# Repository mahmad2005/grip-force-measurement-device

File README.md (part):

# Hand Grip Force and Trajectory Measurement System

## Overview

This project focuses on the development of a portable, intelligent device designed to measure **hand grip force** and **object trajectory** for neurological assessment, particularly in patients with **stroke** or **Multiple Sclerosis (MS)**.

## Key Features

- 🧠 **Neurological Focus**  
  Designed to evaluate motor function, coordination, and rehabilitation progress in stroke and MS patients.

- 🔧 **Core Technologies**
  - **STM32 Microcontrollers** – Real-time data acquisition and processing
  - **Pressure Sensors** – High-resolution spatial grip force measurement
  - **Gyroscope & IMU Sensors** – Motion and orientation tracking of held objects
  - **Bluetooth** – Wireless data transmission to PC/mobile apps
  - **RTOS** – Deterministic multitasking on embedded systems
  - **Embedded Linux** – Advanced data handling and UI support

## System Architecture

[ Pressure Sensor ] [ Gyroscope / IMU ]
| |
[ Analog Front End ] |
| |
[ STM32 MCU ] <--> [ Bluetooth Module ]
|
[ Data Logger / Wi-Fi ]
|
[ Embedded Linux Platform ]

## Use Case

The system enables clinicians and researchers to:
- Quantitatively assess hand grip strength and control
- Track and visualize object movement during gripping tasks
- Analyze neuromuscular impairments and rehabilitation outcomes

## Future Work

- 🔬 Integration with AI models for predictive analysis  
- 📱 Mobile app for real-time data visualization  
- 🌐 Cloud-based data synchronization and reporting

---

**Developed using:**  
`C/C++ (STM32 HAL)`, `FreeRTOS`, `Python`, `Embedded Linux`, `Bluetooth Low Energy (BLE)`

---

> 📍 *This project is part of ongoing research in neuromuscular assessment and assistive rehabilitation technology.*

## � Developer Docs and Quick Start

- Protocol and wiring details (pins, SPI/UDP framing): `docs/System_Protocol_and_Wiring.md`
- Hardware overview and BOM highlights: `hardware/README.md`

Visualizer quick start (Windows cmd):

1) Install Python packages
  - Open a terminal and run:
    - `python -m pip install -r software\requirements.txt`
2) Set your listen IP/port in `software\viz_config.json` if needed (defaults to 0.0.0.0:12345)
3) Run the visualizer
  - `python software\run_visualizer.py`

Make sure the ESP32 sketch `firmware/esp32/ESP32_C3_Zero_SPI_2048_UDP.ino` has `udpAddress` set to your PC’s IP.

## �🔧 New Design

This section features the redesigned pressure sensor and control PCB with updated layout and schematic.

| Front View | Back View |
|------------|------------|
|  |  |
|  |  |

### 🧩 Schematic

### 3D View of the Pressure Sensor Pad

## 📂 Previous Design

This section showcases the earlier versions of the PCB and sensor module designs for the Hand Grip Force Measurement Device.

| 3D View | 3D View (with Bluetooth Module) |
|--------|-------------------------------|
|  |  |

| PCB Layout | PCB Layout (with Bluetooth Module) |
|------------|------------------------------------|
|  |  |

### 🧪 Assembly and Testing Photos

These images capture key stages of the prototype development, including hardware assembly, sensor components, and testing setup.

| Internal Circuit | Grip Force Testing | PCB in Action |
|------------------|--------------------|---------------|
|  |  |  |

These photos show physical testing and assembly steps:
- Internal circuit mounted inside a cylindrical 3D-printed case.
- Testing hand grip force with the pressure sensor system connected to a display.
- Powered PCB with Bluetooth module running in real hardware.

| Pressure Sensor Pad | Pressure Sensing Demo |
|---------------------|------------------------|
|  |  |

## Application View

Below is a sample visualization of the grip force device showing the **32×64 pressure map** along with gyroscope, accelerometer, and magnetometer data:

## 🎥 Demonstration Video

**Real-Time AprilTag Cylinder Tracking with 2D/3D Overlap Visualization**

Click the image above to watch the demonstration video on YouTube.

## 📄 Video Description

This video demonstrates a **real-time vision-based tracking system** using **AprilTags** to estimate and visualize the position of a cylindrical object.  
The system overlays **2D and 3D representations** to show precise alignment and movement tracking, supporting validation of object trajectory and spatial accuracy for experimental and rehabilitation-focused applications.

---

## 🎬 Recent Updates & New Demonstration

### New GripForce 3D Viewer Demo

**Watch the new 3D Viewer software demonstration:**  
[GripForce 3D Viewer Software Outlook – YouTube](https://www.youtube.com/watch?v=9zOydEpcdT4)

This video showcases the updated **3D visualization interface** with improved **pressure heatmap display**, **real-time IMU data plots**, and **orientation cylinder rendering**.

### Updated 3D Simulator Visual

A new high-resolution screenshot showing the **GripForce 3D Simulator interface** is now available:

**Recent updates:** Improve viewer sync, graph zoom, and persistent panel layout

This demonstrates the enhanced UI with:
- Realistic 3D pressure blob movement
- Real-time gyroscope, accelerometer, and magnetometer traces
- 3D orientation object (cylinder) rendering
- Adjustable FPS and parameter controls

---

## 🖥️ Application Components

### Pressure Distribution Visualization

- **32×64 heatmap** showing live grip force across the entire sensor pad
- **Adaptive color scaling** with configurable min/max pressure (default: 0–4095)
- **Transformation options**: flip, rotate, or half-mirror for sensor orientation
- **Real-time animation** at ~60 fps (configurable)
- **Non-stretching display**: maintains aspect ratio during window resize

### IMU Data Visualization

- **3 simultaneous data streams**:
  - **Gyroscope**: angular velocity (°/s) at ±250 dps
  - **Accelerometer**: linear acceleration (g) at ±2 g
  - **Magnetometer**: magnetic field (µT)
- **Dual plot modes**:
  - **Per-component**: separate traces for X, Y, Z channels
  - **Magnitude-only**: single trace per sensor type
- **Sliding window buffer**: default 800 samples, configurable
- **Real-time animated plots** with live data injection

### 3D Object Orientation

- **Interactive 3D cylinder** representing held object
- **Quaternion-to-rotation-matrix** conversion from IMU orientation
- **Real-time 3D rendering** alongside 2D plots
- **Optional mode**: can be toggled on/off in visualizer

### Simulator (No Hardware Needed)

- **Realistic pressure patterns**: moving circular blobs with velocity
- **Simulated IMU oscillations**: smooth gyro, accel, mag data
- **UDP broadcast**: sends packets identical to real hardware
- **Interactive mode**: optional GUI for parameter control (`simulator_gui.py`)
- **Perfect for testing** without connected hardware

---

## 🌐 Web Viewer & Pose Acquisition

### Standalone Desktop Viewer

A **pywebview-based desktop application** for viewing 4K video annotated with AprilTag pose data:

```bash
# Launch from command line:
python run_viewer_standalone.bat

# Or manually:
python app/device_pose_acquisition/auto_target_detections/viewer_7371/standalone_viewer.py
```

**Features**:
- Frame-by-frame playback of annotated video
- Overlay circles and pose estimation data
- Synchronized pressure and IMU timeline (if available)
- Portable: single HTML file with embedded data

### AprilTag Pose Detection & Video Annotation

Process 4K video to detect **cylinder position and orientation** using AprilTags:

```bash
python app/device_pose_acquisition/auto_target_detections/detect_apriltag_pose_fixed11_4k.py \
  --video input.mp4 \
  --annotated-out output.mp4 \
  --export-viewer-data viewer_folder \
  --process-fps 15
```

**Output**:
- **Annotated MP4**: overlays detected circles and pose estimates
- **Viewer Data JSON**: frame-by-frame detection results
- **Viewer HTML**: self-contained, portable viewer with embedded data

**Optional Processing**:
- `--start-frame N, --end-frame N`: process specific frame range
- `--undistort`: apply camera calibration correction
- `--max-frames 0`: process all frames (default)

### Video Resizing for Web Playback

Optimize annotated videos for browser streaming:

```bash
# 720p
ffmpeg -vf "scale=1280:-2" -c:v libx264 -crf 23 input.mp4 output_720p.mp4

# 360p, 15 fps
ffmpeg -vf "fps=15,scale=-2:360" -c:v libx264 -crf 27 input.mp4 output_360p_15fps.mp4

# 240p, 15 fps
ffmpeg -vf "fps=15,scale=-2:240" -c:v libx264 -crf 28 input.mp4 output_240p_15fps.mp4
```

---

## 📁 App Folder Contents & File Guide

### `app/` Directory Structure

```
app/
├── app_view.png                           # Screenshot of pressure + IMU visualizer
├── new_gripforce_3dsimulator_outlook.png  # New 3D simulator interface screenshot
├── 3dsimulator_view.png                   # 3D simulator demo view
├── README.md                              # App-specific documentation
│
├── device_data_acquisitiom/               # Real-time data acquisition & visualization
│   ├── simulator.py                       # Simulates realistic pressure/IMU data (no hardware)
│   ├── simulator_gui.py                   # Interactive GUI for simulator
│   ├── viz_full_with_gyro_accel_mag.py    # Standard 2D visualizer
│   ├── viz_full_with_gyro_accel_mag_3Dobj.py  # 2D visualizer + 3D cylinder
│   ├── run_viz_app.bat                    # Launcher for standard visualizer
│   ├── run_viz_3D.bat                     # Launcher for 3D visualizer
│   └── README.txt                         # Device acquisition documentation
│
└── device_pose_acquisition/               # Video processing & web viewer
    ├── 4k_video_process/
    │   ├── extract_frames.py              # Extract frames from video
    │   ├── manual_reference_circle_alphabet_labeler_4k_best_images.py  # Reference marker UI
    │   ├── sessions/                      # NDJSON pressure/IMU replay data
    │   │   ├── session1.ndjson
    │   │   ├── session_2.ndjson
    │   │   └── ...
    │   └── accuracy_analyzer/
    │       ├── Note.txt                   # Command examples for video processing
    │       └── detect_apriltag_pose_*.py  # Various AprilTag detection scripts
    │
    └── auto_target_detections/
        ├── detect_apriltag_pose_fixed11_4k.py  # Main AprilTag detector (exports viewer data)
        ├── extract_frames.py              # Frame extraction utility
        └── viewer_7371/                   # Web viewer assets
            ├── viewer.html                # Portable viewer template
            ├── viewer_data.json           # Exported frame data
            ├── standalone_viewer.py       # Desktop launcher
            └── session.ndjson, session_2.ndjson  # Example session files
```

### How to Use Each File

| File | Usage |
|------|-------|
| **simulator.py** | Start with `python simulator.py --ip 127.0.0.1 --port 12345 --fps 60` to test visualizer without hardware |
| **viz_full_with_gyro_accel_mag.py** | Main visualizer; shows pressure + IMU data |
| **viz_full_with_gyro_accel_mag_3Dobj.py** | Enhanced visualizer with 3D object rendering |
| **detect_apriltag_pose_fixed11_4k.py** | Process 4K video to export annotated frames and viewer data |
| **viewer.html** | Open in browser or desktop app to view posed video frames |
| **session*.ndjson** | Replay recorded pressure/IMU data; import into analysis tools |

---

## 📊 Data Formats

### Pressure Data

- **32 rows × 64 columns** (2048 total samples per frame)
- **UDP packets**: 10 packets per frame, 205 uint16 values per packet
- **Data type**: uint16, little-endian
- **Range**: 0–4095 (raw 12-bit ADC)
- **Default endpoint**: UDP `0.0.0.0:12345`
- See `docs/System_Protocol_and_Wiring.md` for detailed packet structure

### IMU Data

- **Gyroscope**: ±250 dps (131.0 LSB/deg/s)
- **Accelerometer**: ±2 g (16384.0 LSB/g)
- **Magnetometer**: ±120 µT (0.15 µT/LSB, AK09916 sensor)
- **Update rate**: ~60 fps (synchronized with pressure frames)
- **Format**: big-endian int16 values with header: `b'\xAA\x55IM'`

### Viewer Data (JSON Export)

- **Self-contained HTML** with embedded frame data
- **Per-frame annotations**: circle overlays, pose estimates, detection results
- **Portable format**: open in any browser or desktop viewer
- Generated by `detect_apriltag_pose_fixed11_4k.py --export-viewer-data <path>`

### Session Data (NDJSON)

- **Streaming-safe newline-delimited JSON**
- **One JSON object per line** (metadata + frames)
- **Contains**: frame_idx, timestamp, flattened pressure array, IMU components
- **Schema**: `kinesiology.pressure_imu.ndjson.v1`
- **Use case**: replay in web viewer, time-series analysis

---

## 🎯 Quick Start Guide

### 1. **Test Without Hardware** (Simulator)

```bash
# Terminal 1: Run simulator
cd app/device_data_acquisitiom
python simulator.py --ip 127.0.0.1 --port 12345 --fps 60

# Terminal 2: Run visualizer
python viz_full_with_gyro_accel_mag.py --ip 0.0.0.0 --port 12345 --show-magnitude
```

Or use batch files:
```bash
run_viz_app.bat      # Standard visualizer
run_viz_3D.bat       # 3D visualizer
```

### 2. **Process 4K Video & Export Viewer Data**

```bash
cd app/device_pose_acquisition/auto_target_detections
python detect_apriltag_pose_fixed11_4k.py \
  --video path/to/video.mp4 \
  --annotated-out output.mp4 \
  --export-viewer-data viewer_output
```

Then open `viewer_output/viewer.html` in a browser or desktop viewer.

### 3. **With Real Hardware**

1. Program **ESP32** with `firmware/esp32/ESP32_C3_Zero_SPI_2048_UDP.ino` (set your PC IP)
2. Program **STM32F103C8T6** with firmware in `firmware/stm32f103c8t6/`
3. Connect pressure sensor pad to multiplexer chain (see pinouts in `docs/System_Protocol_and_Wiring.md`)
4. Run visualizer:
   ```bash
   python viz_full_with_gyro_accel_mag.py --ip 0.0.0.0 --port 12345 --show-magnitude
   ```

---

## 📖 Full Project Documentation

For comprehensive technical details, see:

- **[INSTRUCTIONS.md](INSTRUCTIONS.md)** — Project rules, data formats, development guidelines
- **[docs/System_Protocol_and_Wiring.md](docs/System_Protocol_and_Wiring.md)** — Pinouts, SPI/UDP packet structure, timing specs
- **[hardware/README.md](hardware/README.md)** — KiCad project, BOM, component references
- **[app/README.md](app/README.md)** — Visualizer usage, simulator commands, viewer workflow

---

## ❓ Frequently Asked Questions

**Q: Can I use the system without hardware?**  
A: Yes! Run the simulator (`simulator.py`) to generate realistic pressure and IMU data.

**Q: What video formats are supported?**  
A: MP4, MOV, AVI (via OpenCV). 4K video (3840×2160) is recommended for AprilTag detection.

**Q: How do I export data for statistical analysis?**  
A: Use NDJSON session files (see Session Data format) or export viewer JSON. Both are Python/R compatible.

**Q: Can I visualize multiple sessions simultaneously?**  
A: Not in the current version. Planned for future releases.

**Q: Is there a mobile app?**  
A: Mobile support is planned for future versions. Currently PC-only (Windows/Linux/Mac).

---

## 📝 Notes from Previous Work

*Summarized from `app/device_pose_acquisition/4k_video_process/accuracy_analyzer/Note.txt`:*

### AprilTag Processing: Script Variants & Frame Range Control

The project includes **three AprilTag detection script variants**. Choose based on your needs:

#### Script Variants

| Script | Use Case | Key Features |
|--------|----------|--------------|
| **detect_apriltag_pose_fixed11_4k.py** | Main production script | Full video processing, camera matrix auto-scaling |
| **detect_apriltag_pose_fixed11_4k_option3_single_state.py** | Simplified variant | Fewer options, single tracking mode |
| **detect_apriltag_pose_fixed11_4k_option3_single_state_start_end_frame.py** | **Best for testing/partial processing** | Frame range control (`--start-frame`, `--end-frame`) |

#### Key Parameters Explained

- **`--start-frame N`** — Begin processing at frame N (1-based). Default: 1
- **`--end-frame N`** — Stop processing at frame N, inclusive. Default: 0 (process until video ends)
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
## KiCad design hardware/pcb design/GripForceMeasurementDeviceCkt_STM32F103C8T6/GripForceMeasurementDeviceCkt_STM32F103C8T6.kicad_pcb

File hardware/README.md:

# Hardware overview

This folder contains the KiCad project, 3D models, and prior design assets for the Grip Force Measurement Device.

## KiCad project

Project: `pcb design/GripForceMeasurementDeviceCkt_STM32F103C8T6/`

Key files:
- `GripForceMeasurementDeviceCkt_STM32F103C8T6.kicad_sch` — schematic
- `GripForceMeasurementDeviceCkt_STM32F103C8T6.kicad_pcb` — board layout
- `GripForceMeasurementDeviceCkt_STM32F103C8T6.pdf` — exported drawing/PDF (present)
- `gerberAll/` — manufacturing outputs

3D models and references: see `pcb design/3D-Models-Step-files/`

## BOM highlights (from IPC-2581 XML)

- MCU: STM32F103C8Tx (LQFP‑48)
- Multiplexers: ADG732BSUZ (16‑to‑1 analog switch, multiple devices used to reach 32×64)
- Wireless module: ESP32‑C3‑Mini (through‑hole variant footprint)
- IMU header: SparkFun ICM‑20948 module (6‑pin socket)

For a full BOM, open the KiCad project or review the IPC‑2581 XML at:
`pcb design/GripForceMeasurementDeviceCkt_STM32F103C8T6/GripForceMeasurementDeviceCkt_STM32F103C8T6.xml`

## Notes

- Signal levels are 3V3.
- SPI runs between ESP32‑C3 (master) and STM32F103 (slave). Ensure a clean ground reference and short interconnects.
- The sensor matrix connects to the ADG732 network; ADC measures on PA0.

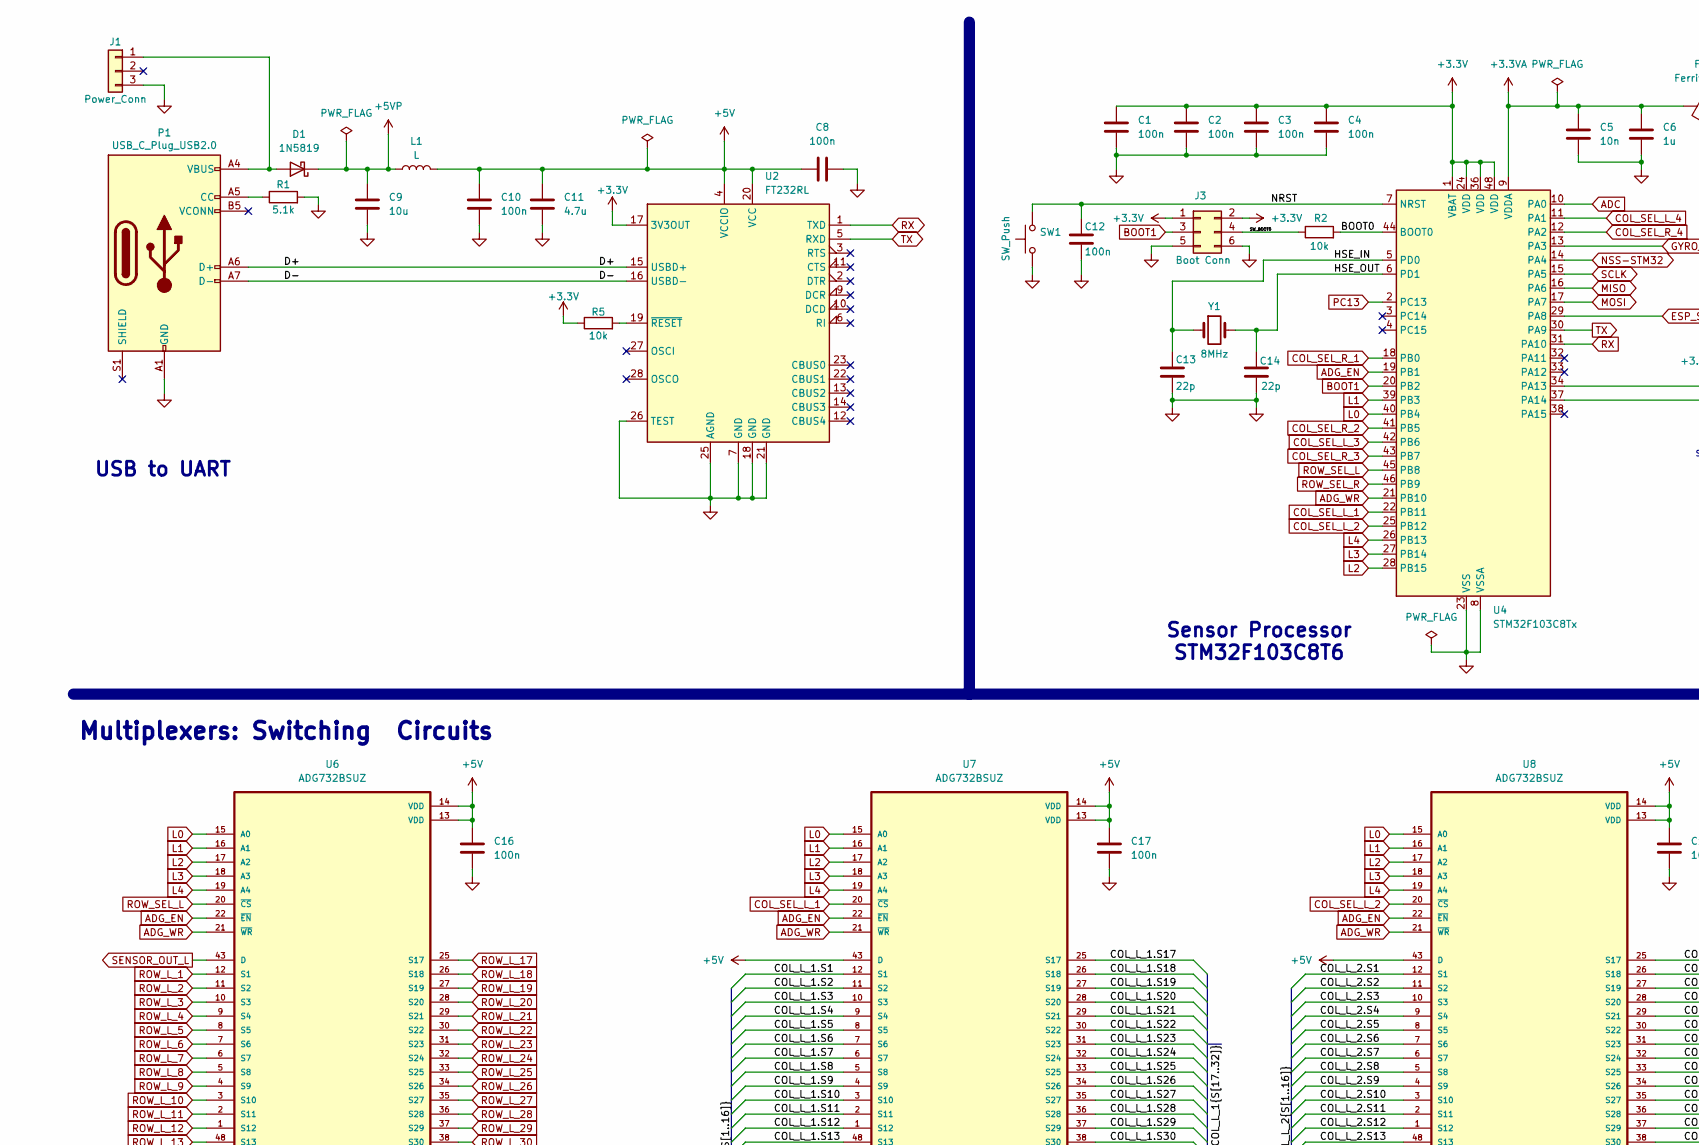
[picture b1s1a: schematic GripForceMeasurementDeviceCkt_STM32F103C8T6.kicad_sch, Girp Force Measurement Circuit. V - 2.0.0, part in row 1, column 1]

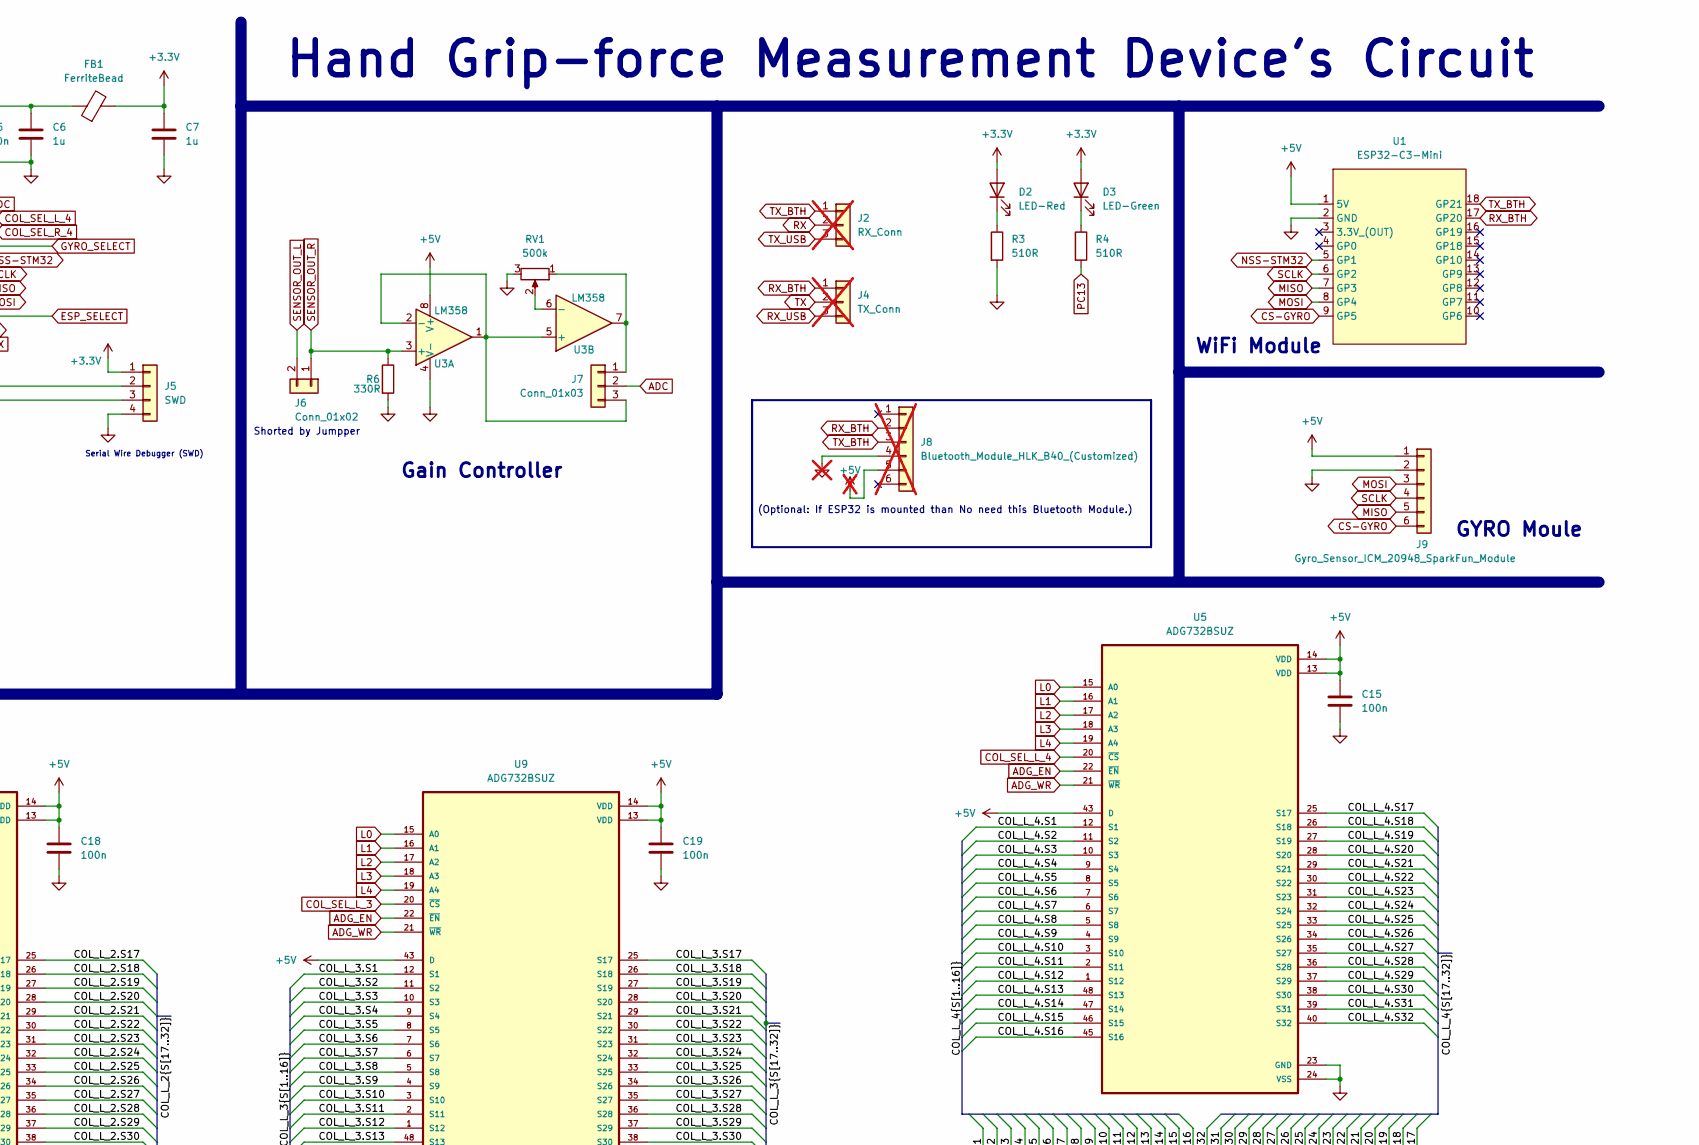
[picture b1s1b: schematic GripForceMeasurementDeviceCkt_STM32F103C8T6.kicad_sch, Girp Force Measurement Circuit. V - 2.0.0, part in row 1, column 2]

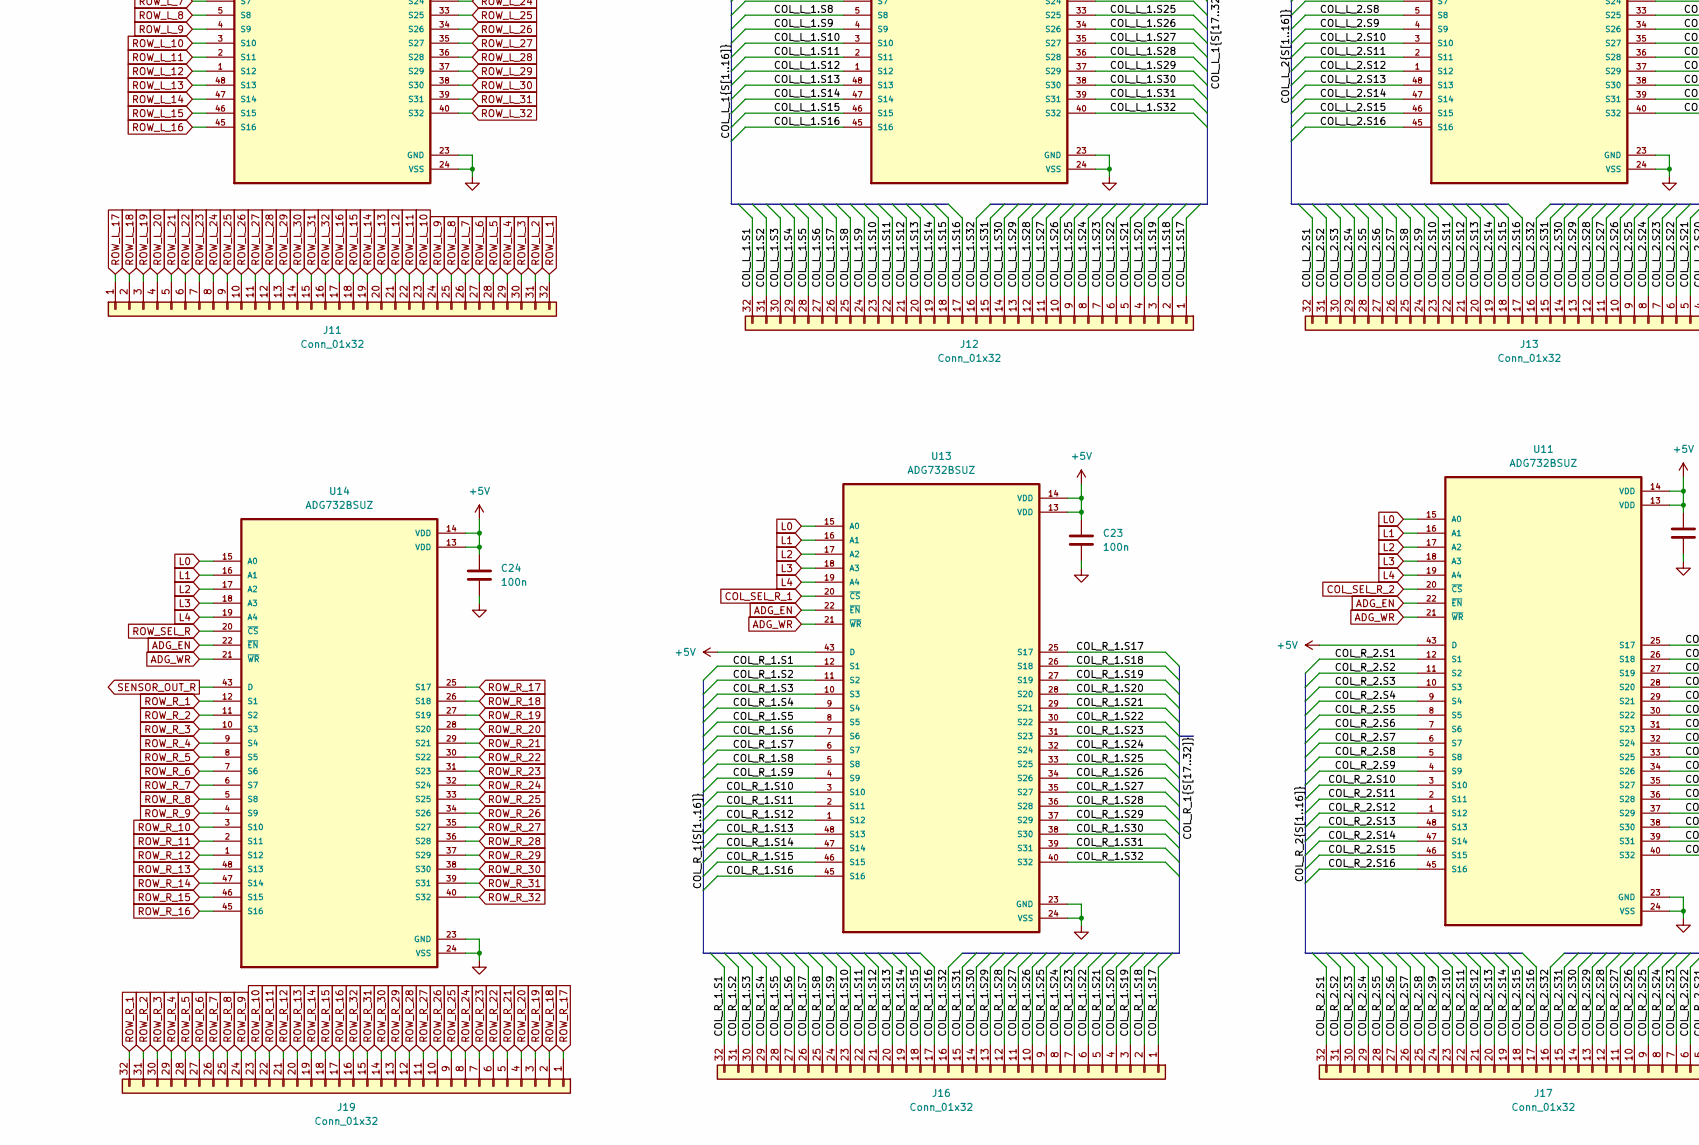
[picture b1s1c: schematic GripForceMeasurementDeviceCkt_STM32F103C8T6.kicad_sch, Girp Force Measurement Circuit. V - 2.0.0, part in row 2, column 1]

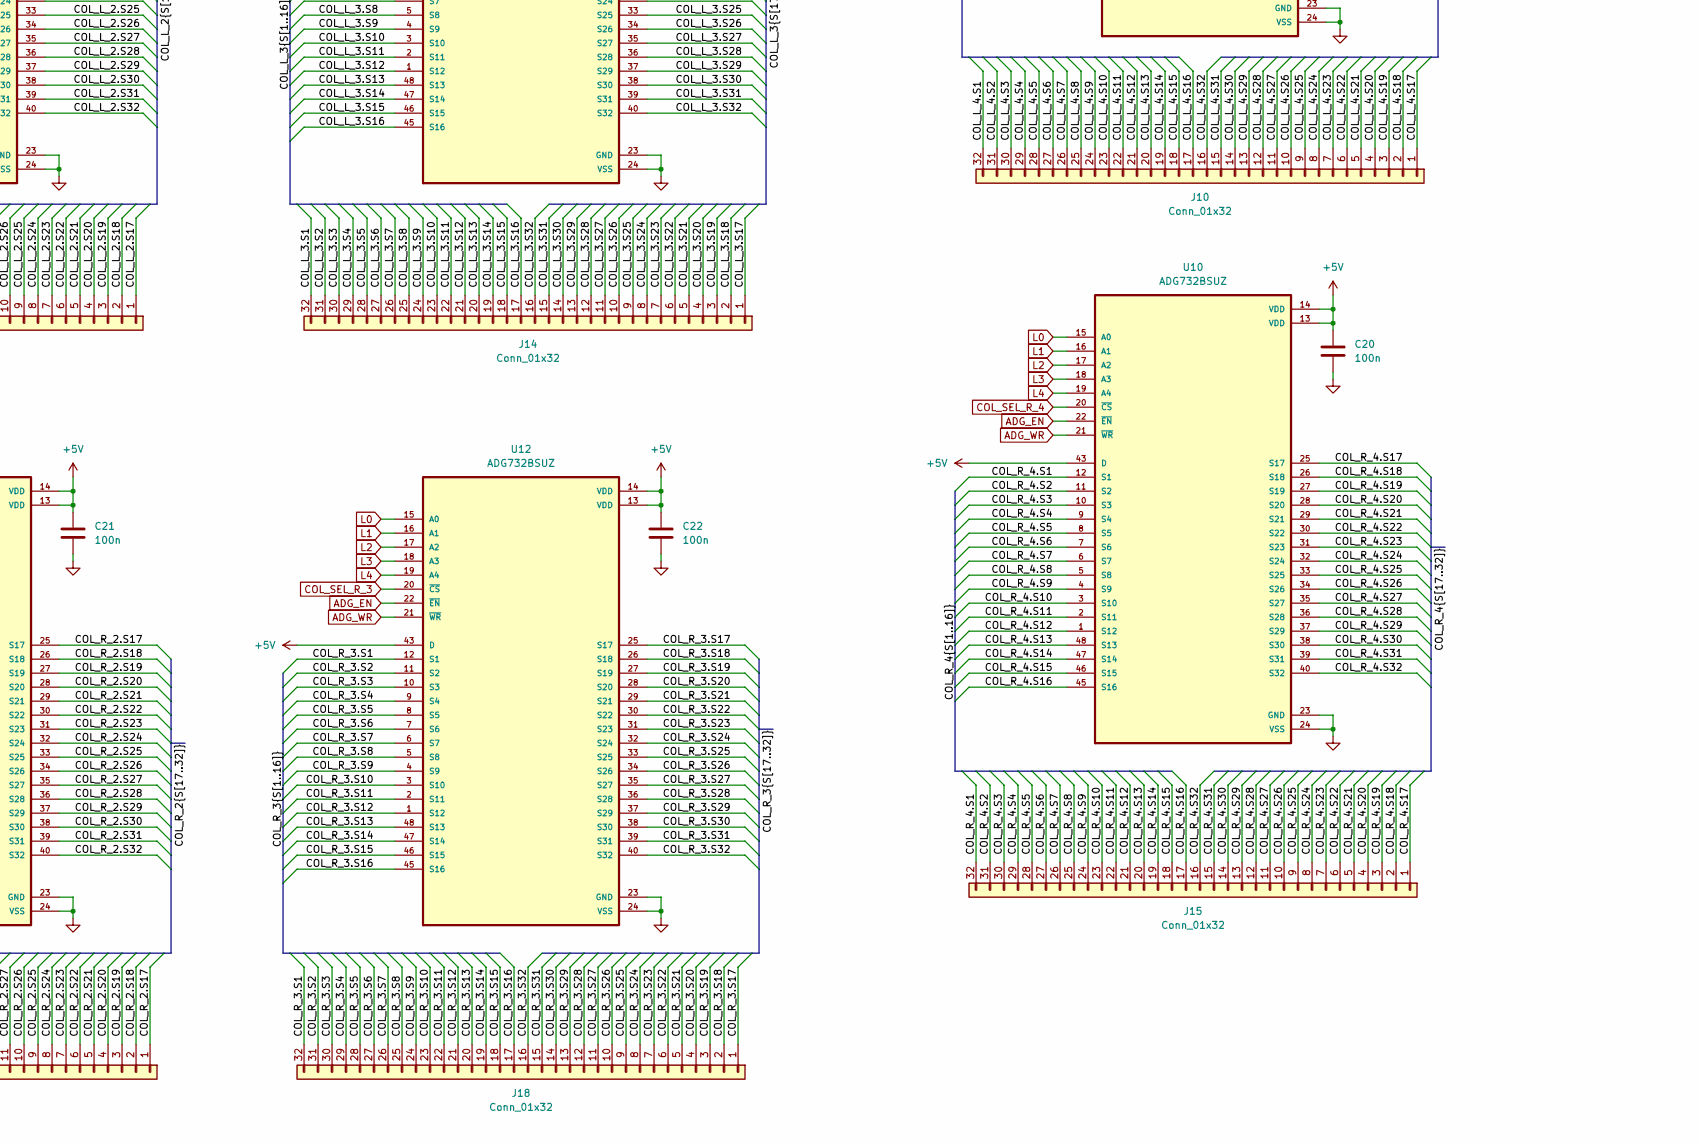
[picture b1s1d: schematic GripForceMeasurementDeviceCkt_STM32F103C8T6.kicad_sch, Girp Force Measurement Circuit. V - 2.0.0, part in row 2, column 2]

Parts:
C1, C2, C3, C4, C8, C10, C12, C15, C16, C17, C18, C19, C20, C21, C22, C23, C24: 100n; C_0603_1608Metric; JLCPCB Part # C14663
C5: 10n; C_0603_1608Metric; JLCPCB Part # C57112
C6, C7: 1u; C_0603_1608Metric; JLCPCB Part # C15849
C9: 10u; C_1206_3216Metric; JLCPCB Part # C13585
C11: 4.7u; C_1206_3216Metric; JLCPCB Part # C29823
C13, C14: 22p; C_0603_1608Metric; JLCPCB Part # C105620
D1: 1N5819; D_SOD-323_HandSoldering; JLCPCB Part # C6067464
D2: LED-Red; LED_0603_1608Metric; JLCPCB Part # C5355420, C5355434
D3: LED-Green; LED_0603_1608Metric; JLCPCB Part # C19171301
FB1: FerriteBead; L_0805_2012Metric; JLCPCB Part # C85840
J1: Power_Conn; PinHeader_1x03_P2.54mm_Vertical; JLCPCB Part # C706875
J2: RX_Conn; PinHeader_1x03_P2.54mm_Vertical; not fitted
J3: Boot Conn; PinHeader_2x03_P2.54mm_Vertical; JLCPCB Part # C7501274
J4: TX_Conn; PinHeader_1x03_P2.54mm_Vertical; not fitted
J5: SWD; PinHeader_1x04_P2.54mm_Vertical; JLCPCB Part # C2691448
J6: Conn_01x02; PinHeader_1x02_P2.54mm_Vertical; JLCPCB Part # C706874
J7: Conn_01x03; PinHeader_1x03_P2.54mm_Vertical; JLCPCB Part # C706875
J8: Bluetooth_Module_HLK_B40_(Customized); PinSocket_1x06_P2.54mm_Vertical; not fitted
J9: Gyro_Sensor_ICM_20948_SparkFun_Module; PinSocket_1x06_P2.54mm_Vertical; JLCPCB Part # C6332199
J10, J11, J12, J13, J14, J15, J16, J17, J18, J19: Conn_01x32; Hirose_FH12-32S-0.5SH_1x32-1MP_P0.50mm_Horizontal; JLCPCB Part # C262672
L1: L; L_0603_1608Metric; JLCPCB Part # C139179
P1: USB_C_Plug_USB2.0; USB_C_Receptacle_Amphenol_12401610E4-2A; JLCPCB Part # C5119948
R1: 5.1k; R_0603_1608Metric; JLCPCB Part # C23186
R2, R5: 10k; R_0603_1608Metric; JLCPCB Part # C25804
R3, R4: 510R; R_0603_1608Metric; JLCPCB Part # C2073794
R6: 330R; R_Axial_DIN0207_L6.3mm_D2.5mm_P10.16mm_Horizontal; JLCPCB Part # C173152
RV1: 500k; Potentiometer_Bourns_3296W_Vertical; JLCPCB Part # C118921
SW1: SW_Push; SW_Tactile_SPST_NO_Straight_CK_PTS636Sx25SMTRLFS; JLCPCB Part # C318938
U1: ESP32-C3-Mini; ESP32-C3-Mini-through-hole
U2: FT232RL; SSOP-28_5.3x10.2mm_P0.65mm; JLCPCB Part # C8690
U3: LM358; SO-8_3.9x4.9mm_P1.27mm; JLCPCB Part # C5296727
U4: STM32F103C8Tx; LQFP-48_7x7mm_P0.5mm; JLCPCB Part # C8734
U5, U6, U7, U8, U9, U10, U11, U12, U13, U14: ADG732BSUZ; TQFP-48_7x7mm_P0.5mm; JLCPCB Part # C114845
Y1: 8MHz; Crystal_HC49-4H_Vertical; JLCPCB Part # C21263

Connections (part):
+3.3V: C1.1, C2.1, C3.1, C4.1, C7.1, D2.2 (A), D3.2 (A), FB1.2, J3.1, J3.2, J5.1, R5.1, U2.17 (3V3OUT), U4.1 (VBAT), U4.24 (VDD), U4.36 (VDD), U4.48 (VDD)
+3.3VA: C5.1, C6.1, FB1.1, U4.9 (VDDA)
+5V: C8.2, C10.1, C11.1, C15.1, C16.1, C17.1, C18.1, C19.1, C20.1, C21.1, C22.1, C23.1, C24.1, J8.5, J9.1, L1.2, U1.1 (5V), U2.4 (VCCIO), U2.20 (VCC), U3.8 (V+), U5.13 (VDD), U5.14 (VDD), U5.43 (D), U6.13 (VDD), U6.14 (VDD), U7.13 (VDD), U7.14 (VDD), U7.43 (D), U8.13 (VDD), U8.14 (VDD), U8.43 (D), U9.13 (VDD), U9.14 (VDD), U9.43 (D), U10.13 (VDD), U10.14 (VDD), U10.43 (D), U11.13 (VDD), U11.14 (VDD), U11.43 (D), U12.13 (VDD), U12.14 (VDD), U12.43 (D), U13.13 (VDD), U13.14 (VDD), U13.43 (D), U14.13 (VDD), U14.14 (VDD)
+5VP: C9.1, D1.1 (K), L1.1
/BOOT0: R2.2, U4.44 (BOOT0)
/COL_L_1.S1: J12.32, U7.12 (S1)
/COL_L_1.S2: J12.31, U7.11 (S2)
/COL_L_1.S3: J12.30, U7.10 (S3)
/COL_L_1.S4: J12.29, U7.9 (S4)
/COL_L_1.S5: J12.28, U7.8 (S5)
/COL_L_1.S6: J12.27, U7.7 (S6)
/COL_L_1.S7: J12.26, U7.6 (S7)
/COL_L_1.S8: J12.25, U7.5 (S8)
/COL_L_1.S9: J12.24, U7.4 (S9)
/COL_L_1.S10: J12.23, U7.3 (S10)
/COL_L_1.S11: J12.22, U7.2 (S11)
/COL_L_1.S12: J12.21, U7.1 (S12)
/COL_L_1.S13: J12.20, U7.48 (S13)
/COL_L_1.S14: J12.19, U7.47 (S14)
/COL_L_1.S15: J12.18, U7.46 (S15)
/COL_L_1.S16: J12.17, U7.45 (S16)
/COL_L_1.S17: J12.1, U7.25 (S17)
/COL_L_1.S18: J12.2, U7.26 (S18)
/COL_L_1.S19: J12.3, U7.27 (S19)
/COL_L_1.S20: J12.4, U7.28 (S20)
/COL_L_1.S21: J12.5, U7.29 (S21)
/COL_L_1.S22: J12.6, U7.30 (S22)
/COL_L_1.S23: J12.7, U7.31 (S23)
/COL_L_1.S24: J12.8, U7.32 (S24)
/COL_L_1.S25: J12.9, U7.33 (S25)
/COL_L_1.S26: J12.10, U7.34 (S26)
/COL_L_1.S27: J12.11, U7.35 (S27)
/COL_L_1.S28: J12.12, U7.36 (S28)
/COL_L_1.S29: J12.13, U7.37 (S29)
/COL_L_1.S30: J12.14, U7.38 (S30)
/COL_L_1.S31: J12.15, U7.39 (S31)
/COL_L_1.S32: J12.16, U7.40 (S32)
/COL_L_2.S1: J13.32, U8.12 (S1)
/COL_L_2.S2: J13.31, U8.11 (S2)
/COL_L_2.S3: J13.30, U8.10 (S3)
/COL_L_2.S4: J13.29, U8.9 (S4)
/COL_L_2.S5: J13.28, U8.8 (S5)
/COL_L_2.S6: J13.27, U8.7 (S6)
/COL_L_2.S7: J13.26, U8.6 (S7)
/COL_L_2.S8: J13.25, U8.5 (S8)
/COL_L_2.S9: J13.24, U8.4 (S9)
/COL_L_2.S10: J13.23, U8.3 (S10)
/COL_L_2.S11: J13.22, U8.2 (S11)
/COL_L_2.S12: J13.21, U8.1 (S12)
/COL_L_2.S13: J13.20, U8.48 (S13)
/COL_L_2.S14: J13.19, U8.47 (S14)
/COL_L_2.S15: J13.18, U8.46 (S15)
/COL_L_2.S16: J13.17, U8.45 (S16)
/COL_L_2.S17: J13.1, U8.25 (S17)
/COL_L_2.S18: J13.2, U8.26 (S18)
/COL_L_2.S19: J13.3, U8.27 (S19)
/COL_L_2.S20: J13.4, U8.28 (S20)
/COL_L_2.S21: J13.5, U8.29 (S21)
/COL_L_2.S22: J13.6, U8.30 (S22)
/COL_L_2.S23: J13.7, U8.31 (S23)
/COL_L_2.S24: J13.8, U8.32 (S24)
/COL_L_2.S25: J13.9, U8.33 (S25)
/COL_L_2.S26: J13.10, U8.34 (S26)
/COL_L_2.S27: J13.11, U8.35 (S27)
/COL_L_2.S28: J13.12, U8.36 (S28)
/COL_L_2.S29: J13.13, U8.37 (S29)
/COL_L_2.S30: J13.14, U8.38 (S30)
/COL_L_2.S31: J13.15, U8.39 (S31)
/COL_L_2.S32: J13.16, U8.40 (S32)
/COL_L_3.S1: J14.32, U9.12 (S1)
/COL_L_3.S2: J14.31, U9.11 (S2)
/COL_L_3.S3: J14.30, U9.10 (S3)
/COL_L_3.S4: J14.29, U9.9 (S4)
/COL_L_3.S5: J14.28, U9.8 (S5)
/COL_L_3.S6: J14.27, U9.7 (S6)
/COL_L_3.S7: J14.26, U9.6 (S7)
/COL_L_3.S8: J14.25, U9.5 (S8)
/COL_L_3.S9: J14.24, U9.4 (S9)
/COL_L_3.S10: J14.23, U9.3 (S10)
/COL_L_3.S11: J14.22, U9.2 (S11)
/COL_L_3.S12: J14.21, U9.1 (S12)
/COL_L_3.S13: J14.20, U9.48 (S13)
/COL_L_3.S14: J14.19, U9.47 (S14)
/COL_L_3.S15: J14.18, U9.46 (S15)
/COL_L_3.S16: J14.17, U9.45 (S16)
/COL_L_3.S17: J14.1, U9.25 (S17)
/COL_L_3.S18: J14.2, U9.26 (S18)
/COL_L_3.S19: J14.3, U9.27 (S19)
/COL_L_3.S20: J14.4, U9.28 (S20)
/COL_L_3.S21: J14.5, U9.29 (S21)
/COL_L_3.S22: J14.6, U9.30 (S22)
/COL_L_3.S23: J14.7, U9.31 (S23)
/COL_L_3.S24: J14.8, U9.32 (S24)
/COL_L_3.S25: J14.9, U9.33 (S25)
/COL_L_3.S26: J14.10, U9.34 (S26)
/COL_L_3.S27: J14.11, U9.35 (S27)
/COL_L_3.S28: J14.12, U9.36 (S28)
/COL_L_3.S29: J14.13, U9.37 (S29)
/COL_L_3.S30: J14.14, U9.38 (S30)
/COL_L_3.S31: J14.15, U9.39 (S31)
/COL_L_3.S32: J14.16, U9.40 (S32)
/COL_L_4.S1: J10.32, U5.12 (S1)
/COL_L_4.S2: J10.31, U5.11 (S2)
/COL_L_4.S3: J10.30, U5.10 (S3)
/COL_L_4.S4: J10.29, U5.9 (S4)
/COL_L_4.S5: J10.28, U5.8 (S5)
/COL_L_4.S6: J10.27, U5.7 (S6)
/COL_L_4.S7: J10.26, U5.6 (S7)
/COL_L_4.S8: J10.25, U5.5 (S8)
/COL_L_4.S9: J10.24, U5.4 (S9)
/COL_L_4.S10: J10.23, U5.3 (S10)
/COL_L_4.S11: J10.22, U5.2 (S11)
/COL_L_4.S12: J10.21, U5.1 (S12)
/COL_L_4.S13: J10.20, U5.48 (S13)
/COL_L_4.S14: J10.19, U5.47 (S14)
/COL_L_4.S15: J10.18, U5.46 (S15)
/COL_L_4.S16: J10.17, U5.45 (S16)
/COL_L_4.S17: J10.1, U5.25 (S17)
/COL_L_4.S18: J10.2, U5.26 (S18)
/COL_L_4.S19: J10.3, U5.27 (S19)
/COL_L_4.S20: J10.4, U5.28 (S20)
/COL_L_4.S21: J10.5, U5.29 (S21)
/COL_L_4.S22: J10.6, U5.30 (S22)
/COL_L_4.S23: J10.7, U5.31 (S23)
/COL_L_4.S24: J10.8, U5.32 (S24)
/COL_L_4.S25: J10.9, U5.33 (S25)
/COL_L_4.S26: J10.10, U5.34 (S26)
/COL_L_4.S27: J10.11, U5.35 (S27)
/COL_L_4.S28: J10.12, U5.36 (S28)
/COL_L_4.S29: J10.13, U5.37 (S29)
/COL_L_4.S30: J10.14, U5.38 (S30)
/COL_L_4.S31: J10.15, U5.39 (S31)
/COL_L_4.S32: J10.16, U5.40 (S32)
/COL_R_1.S1: J16.32, U13.12 (S1)
/COL_R_1.S2: J16.31, U13.11 (S2)
/COL_R_1.S3: J16.30, U13.10 (S3)
/COL_R_1.S4: J16.29, U13.9 (S4)
/COL_R_1.S5: J16.28, U13.8 (S5)
/COL_R_1.S6: J16.27, U13.7 (S6)
/COL_R_1.S7: J16.26, U13.6 (S7)
/COL_R_1.S8: J16.25, U13.5 (S8)
/COL_R_1.S9: J16.24, U13.4 (S9)
/COL_R_1.S10: J16.23, U13.3 (S10)
/COL_R_1.S11: J16.22, U13.2 (S11)
/COL_R_1.S12: J16.21, U13.1 (S12)
/COL_R_1.S13: J16.20, U13.48 (S13)
/COL_R_1.S14: J16.19, U13.47 (S14)
/COL_R_1.S15: J16.18, U13.46 (S15)
/COL_R_1.S16: J16.17, U13.45 (S16)
/COL_R_1.S17: J16.1, U13.25 (S17)
/COL_R_1.S18: J16.2, U13.26 (S18)
/COL_R_1.S19: J16.3, U13.27 (S19)
/COL_R_1.S20: J16.4, U13.28 (S20)
/COL_R_1.S21: J16.5, U13.29 (S21)
/COL_R_1.S22: J16.6, U13.30 (S22)
/COL_R_1.S23: J16.7, U13.31 (S23)
/COL_R_1.S24: J16.8, U13.32 (S24)
/COL_R_1.S25: J16.9, U13.33 (S25)
/COL_R_1.S26: J16.10, U13.34 (S26)
/COL_R_1.S27: J16.11, U13.35 (S27)
/COL_R_1.S28: J16.12, U13.36 (S28)
/COL_R_1.S29: J16.13, U13.37 (S29)
/COL_R_1.S30: J16.14, U13.38 (S30)
/COL_R_1.S31: J16.15, U13.39 (S31)
/COL_R_1.S32: J16.16, U13.40 (S32)
/COL_R_2.S1: J17.32, U11.12 (S1)
/COL_R_2.S2: J17.31, U11.11 (S2)
/COL_R_2.S3: J17.30, U11.10 (S3)
/COL_R_2.S4: J17.29, U11.9 (S4)
/COL_R_2.S5: J17.28, U11.8 (S5)
/COL_R_2.S6: J17.27, U11.7 (S6)
/COL_R_2.S7: J17.26, U11.6 (S7)
/COL_R_2.S8: J17.25, U11.5 (S8)
/COL_R_2.S9: J17.24, U11.4 (S9)
/COL_R_2.S10: J17.23, U11.3 (S10)
/COL_R_2.S11: J17.22, U11.2 (S11)
/COL_R_2.S12: J17.21, U11.1 (S12)
/COL_R_2.S13: J17.20, U11.48 (S13)
/COL_R_2.S14: J17.19, U11.47 (S14)
/COL_R_2.S15: J17.18, U11.46 (S15)
/COL_R_2.S16: J17.17, U11.45 (S16)
/COL_R_2.S17: J17.1, U11.25 (S17)
/COL_R_2.S18: J17.2, U11.26 (S18)
/COL_R_2.S19: J17.3, U11.27 (S19)
/COL_R_2.S20: J17.4, U11.28 (S20)
/COL_R_2.S21: J17.5, U11.29 (S21)
/COL_R_2.S22: J17.6, U11.30 (S22)
/COL_R_2.S23: J17.7, U11.31 (S23)
/COL_R_2.S24: J17.8, U11.32 (S24)
/COL_R_2.S25: J17.9, U11.33 (S25)
/COL_R_2.S26: J17.10, U11.34 (S26)
/COL_R_2.S27: J17.11, U11.35 (S27)
/COL_R_2.S28: J17.12, U11.36 (S28)
/COL_R_2.S29: J17.13, U11.37 (S29)
/COL_R_2.S30: J17.14, U11.38 (S30)
/COL_R_2.S31: J17.15, U11.39 (S31)
/COL_R_2.S32: J17.16, U11.40 (S32)
/COL_R_3.S1: J18.32, U12.12 (S1)
/COL_R_3.S2: J18.31, U12.11 (S2)
/COL_R_3.S3: J18.30, U12.10 (S3)
/COL_R_3.S4: J18.29, U12.9 (S4)
/COL_R_3.S5: J18.28, U12.8 (S5)
/COL_R_3.S6: J18.27, U12.7 (S6)
/COL_R_3.S7: J18.26, U12.6 (S7)
/COL_R_3.S8: J18.25, U12.5 (S8)
/COL_R_3.S9: J18.24, U12.4 (S9)
/COL_R_3.S10: J18.23, U12.3 (S10)
/COL_R_3.S11: J18.22, U12.2 (S11)
/COL_R_3.S12: J18.21, U12.1 (S12)
/COL_R_3.S13: J18.20, U12.48 (S13)
/COL_R_3.S14: J18.19, U12.47 (S14)
/COL_R_3.S15: J18.18, U12.46 (S15)
/COL_R_3.S16: J18.17, U12.45 (S16)
/COL_R_3.S17: J18.1, U12.25 (S17)
/COL_R_3.S18: J18.2, U12.26 (S18)
/COL_R_3.S19: J18.3, U12.27 (S19)
/COL_R_3.S20: J18.4, U12.28 (S20)
/COL_R_3.S21: J18.5, U12.29 (S21)
/COL_R_3.S22: J18.6, U12.30 (S22)
/COL_R_3.S23: J18.7, U12.31 (S23)
/COL_R_3.S24: J18.8, U12.32 (S24)
/COL_R_3.S25: J18.9, U12.33 (S25)
/COL_R_3.S26: J18.10, U12.34 (S26)
/COL_R_3.S27: J18.11, U12.35 (S27)
/COL_R_3.S28: J18.12, U12.36 (S28)
/COL_R_3.S29: J18.13, U12.37 (S29)
/COL_R_3.S30: J18.14, U12.38 (S30)
/COL_R_3.S31: J18.15, U12.39 (S31)
/COL_R_3.S32: J18.16, U12.40 (S32)
/COL_R_4.S1: J15.32, U10.12 (S1)
/COL_R_4.S2: J15.31, U10.11 (S2)
/COL_R_4.S3: J15.30, U10.10 (S3)
/COL_R_4.S4: J15.29, U10.9 (S4)
/COL_R_4.S5: J15.28, U10.8 (S5)
/COL_R_4.S6: J15.27, U10.7 (S6)
/COL_R_4.S7: J15.26, U10.6 (S7)
/COL_R_4.S8: J15.25, U10.5 (S8)
/COL_R_4.S9: J15.24, U10.4 (S9)
/COL_R_4.S10: J15.23, U10.3 (S10)
/COL_R_4.S11: J15.22, U10.2 (S11)
/COL_R_4.S12: J15.21, U10.1 (S12)
/COL_R_4.S13: J15.20, U10.48 (S13)
/COL_R_4.S14: J15.19, U10.47 (S14)
/COL_R_4.S15: J15.18, U10.46 (S15)
/COL_R_4.S16: J15.17, U10.45 (S16)
/COL_R_4.S17: J15.1, U10.25 (S17)
/COL_R_4.S18: J15.2, U10.26 (S18)
/COL_R_4.S19: J15.3, U10.27 (S19)
/COL_R_4.S20: J15.4, U10.28 (S20)
/COL_R_4.S21: J15.5, U10.29 (S21)
/COL_R_4.S22: J15.6, U10.30 (S22)
/COL_R_4.S23: J15.7, U10.31 (S23)
/COL_R_4.S24: J15.8, U10.32 (S24)
/COL_R_4.S25: J15.9, U10.33 (S25)
/COL_R_4.S26: J15.10, U10.34 (S26)
/COL_R_4.S27: J15.11, U10.35 (S27)
/COL_R_4.S28: J15.12, U10.36 (S28)
/COL_R_4.S29: J15.13, U10.37 (S29)
/COL_R_4.S30: J15.14, U10.38 (S30)
/COL_R_4.S31: J15.15, U10.39 (S31)
/COL_R_4.S32: J15.16, U10.40 (S32)
/D+: P1.A6 (D+), U2.15 (USBD+)
/D-: P1.A7 (D-), U2.16 (USBD-)
/HSE_IN: C13.1, U4.5 (PD0), Y1.1
/HSE_OUT: C14.1, U4.6 (PD1), Y1.2
/NRST: C12.1, SW1.2, U4.7 (NRST)
/SW_BOOT0: J3.4, R2.1
ADC: J7.2, U4.10 (PA0)
ADG_EN: U4.19 (PB1), U5.22 (~EN), U6.22 (~EN), U7.22 (~EN), U8.22 (~EN), U9.22 (~EN), U10.22 (~EN), U11.22 (~EN), U12.22 (~EN), U13.22 (~EN), U14.22 (~EN)
ADG_WR: U4.21 (PB10), U5.21 (~WR), U6.21 (~WR), U7.21 (~WR), U8.21 (~WR), U9.21 (~WR), U10.21 (~WR), U11.21 (~WR), U12.21 (~WR), U13.21 (~WR), U14.21 (~WR)
BOOT1: J3.3, U4.20 (PB2)
COL_SEL_L_1: U4.22 (PB11), U7.20 (~CS)
COL_SEL_L_2: U4.25 (PB12), U8.20 (~CS)
COL_SEL_L_3: U4.42 (PB6), U9.20 (~CS)
COL_SEL_L_4: U4.11 (PA1), U5.20 (~CS)
COL_SEL_R_1: U4.18 (PB0), U13.20 (~CS)
COL_SEL_R_2: U4.41 (PB5), U11.20 (~CS)
COL_SEL_R_3: U4.43 (PB7), U12.20 (~CS)
COL_SEL_R_4: U4.12 (PA2), U10.20 (~CS)
CS-GYRO: J9.6, U1.9 (GP5)
ESP_SELECT: U4.29 (PA8)
GND: C1.2, C2.2, C3.2, C4.2, C5.2, C6.2, C7.2, C8.1, C9.2, C10.2, C11.2, C12.2, C13.2, C14.2, C15.2, C16.2, C17.2, C18.2, C19.2, C20.2, C21.2, C22.2, C23.2, C24.2, J1.3, J3.5, J3.6, J5.4, J8.4, J9.2, P1.A1 (GND), P1.A12 (GND), P1.B1 (GND), P1.B12 (GND), R1.2, R3.2, R6.2, RV1.3, SW1.1, U1.2 (GND), U2.7 (GND), U2.18 (GND), U2.21 (GND), U2.25 (AGND), U2.26 (TEST), U3.4 (V-), U4.8 (VSSA), U4.23 (VSS), U4.35 (VSS), U4.47 (VSS), U5.23 (GND), U5.24 (VSS), U6.23 (GND), U6.24 (VSS), U7.23 (GND), U7.24 (VSS), U8.23 (GND), U8.24 (VSS), U9.23 (GND), U9.24 (VSS), U10.23 (GND), U10.24 (VSS), U11.23 (GND), U11.24 (VSS), U12.23 (GND), U12.24 (VSS), U13.23 (GND), U13.24 (VSS), U14.23 (GND), U14.24 (VSS)
GYRO_SELECT: U4.13 (PA3)
L0: U4.40 (PB4), U5.15 (A0), U6.15 (A0), U7.15 (A0), U8.15 (A0), U9.15 (A0), U10.15 (A0), U11.15 (A0), U12.15 (A0), U13.15 (A0), U14.15 (A0)
L1: U4.39 (PB3), U5.16 (A1), U6.16 (A1), U7.16 (A1), U8.16 (A1), U9.16 (A1), U10.16 (A1), U11.16 (A1), U12.16 (A1), U13.16 (A1), U14.16 (A1)
L2: U4.28 (PB15), U5.17 (A2), U6.17 (A2), U7.17 (A2), U8.17 (A2), U9.17 (A2), U10.17 (A2), U11.17 (A2), U12.17 (A2), U13.17 (A2), U14.17 (A2)
L3: U4.27 (PB14), U5.18 (A3), U6.18 (A3), U7.18 (A3), U8.18 (A3), U9.18 (A3), U10.18 (A3), U11.18 (A3), U12.18 (A3), U13.18 (A3), U14.18 (A3)
L4: U4.26 (PB13), U5.19 (A4), U6.19 (A4), U7.19 (A4), U8.19 (A4), U9.19 (A4), U10.19 (A4), U11.19 (A4), U12.19 (A4), U13.19 (A4), U14.19 (A4)
MISO: J9.5, U1.7 (GP3), U4.16 (PA6)
MOSI: J9.3, U1.8 (GP4), U4.17 (PA7)
NSS-STM32: U1.5 (GP1), U4.14 (PA4)
unnamed: D1.2 (A), J1.1, P1.A4 (VBUS), P1.A9 (VBUS), P1.B4 (VBUS), P1.B9 (VBUS)
unnamed: D2.1 (K), R3.1
unnamed: D3.1 (K), R4.1
unnamed: J5.2, U4.34 (PA13)
unnamed: J5.3, U4.37 (PA14)
unnamed: J7.1, RV1.1, U3.7
unnamed: J7.3, U3.1, U3.2 (-), U3.5 (+)
unnamed: P1.A5 (CC), R1.1
unnamed: R5.2, U2.19 (~RESET)
unnamed: RV1.2, U3.6 (-)
PC13: R4.2, U4.2 (PC13)
ROW_L_1: J11.32, U6.12 (S1)
ROW_L_2: J11.31, U6.11 (S2)
ROW_L_3: J11.30, U6.10 (S3)
ROW_L_4: J11.29, U6.9 (S4)
ROW_L_5: J11.28, U6.8 (S5)
ROW_L_6: J11.27, U6.7 (S6)
ROW_L_7: J11.26, U6.6 (S7)
ROW_L_8: J11.25, U6.5 (S8)
ROW_L_9: J11.24, U6.4 (S9)
ROW_L_10: J11.23, U6.3 (S10)
ROW_L_11: J11.22, U6.2 (S11)
ROW_L_12: J11.21, U6.1 (S12)
ROW_L_13: J11.20, U6.48 (S13)
ROW_L_14: J11.19, U6.47 (S14)
ROW_L_15: J11.18, U6.46 (S15)
ROW_L_16: J11.17, U6.45 (S16)
ROW_L_17: J11.1, U6.25 (S17)
ROW_L_18: J11.2, U6.26 (S18)
ROW_L_19: J11.3, U6.27 (S19)
ROW_L_20: J11.4, U6.28 (S20)
ROW_L_21: J11.5, U6.29 (S21)
ROW_L_22: J11.6, U6.30 (S22)
ROW_L_23: J11.7, U6.31 (S23)
ROW_L_24: J11.8, U6.32 (S24)
ROW_L_25: J11.9, U6.33 (S25)
ROW_L_26: J11.10, U6.34 (S26)
ROW_L_27: J11.11, U6.35 (S27)
ROW_L_28: J11.12, U6.36 (S28)
ROW_L_29: J11.13, U6.37 (S29)
ROW_L_30: J11.14, U6.38 (S30)
ROW_L_31: J11.15, U6.39 (S31)
ROW_L_32: J11.16, U6.40 (S32)
ROW_R_1: J19.32, U14.12 (S1)
ROW_R_2: J19.31, U14.11 (S2)
ROW_R_3: J19.30, U14.10 (S3)
ROW_R_4: J19.29, U14.9 (S4)
ROW_R_5: J19.28, U14.8 (S5)
ROW_R_6: J19.27, U14.7 (S6)
ROW_R_7: J19.26, U14.6 (S7)
ROW_R_8: J19.25, U14.5 (S8)
ROW_R_9: J19.24, U14.4 (S9)
ROW_R_10: J19.23, U14.3 (S10)
ROW_R_11: J19.22, U14.2 (S11)
ROW_R_12: J19.21, U14.1 (S12)
ROW_R_13: J19.20, U14.48 (S13)
ROW_R_14: J19.19, U14.47 (S14)
ROW_R_15: J19.18, U14.46 (S15)
ROW_R_16: J19.17, U14.45 (S16)
ROW_R_17: J19.1, U14.25 (S17)
ROW_R_18: J19.2, U14.26 (S18)
ROW_R_19: J19.3, U14.27 (S19)
ROW_R_20: J19.4, U14.28 (S20)
ROW_R_21: J19.5, U14.29 (S21)
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
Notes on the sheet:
Hand Grip-force Measurement Device's Circuit
Serial Wire Debugger (SWD)
Gain Controller
Sensor Processor STM32F103C8T6
Shorted by Jumpper
GYRO Moule
Multiplexers: Switching Circuits
(Optional: If ESP32 is mounted than No need this Bluetooth Module.)
USB to UART
WiFi Module
